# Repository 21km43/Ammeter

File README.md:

# Ammeter
[INA226](https://datasheet.lcsc.com/lcsc/1809192224_Texas-Instruments-INA226AIDGSR_C49851.pdf)を利用した電流計。主にマイコンの消費電流の測定に利用する。  
性能は以下の通り。動作確認済み。
* 入力電圧: 0~36V
* シャント抵抗値: 100mΩ
* 分解能: 25µA
* 電流上限: 819.2mA

ヒューズは入れていないので過電流には注意すること。  
基板CADは[KiCAD](kicad.org)。また、ガーバーファイルはproduction以下に配置した。JLCPCBにアップロードすればすぐに発注可能。

## LICENSE
[MIT LICENSE](/LICENSE)

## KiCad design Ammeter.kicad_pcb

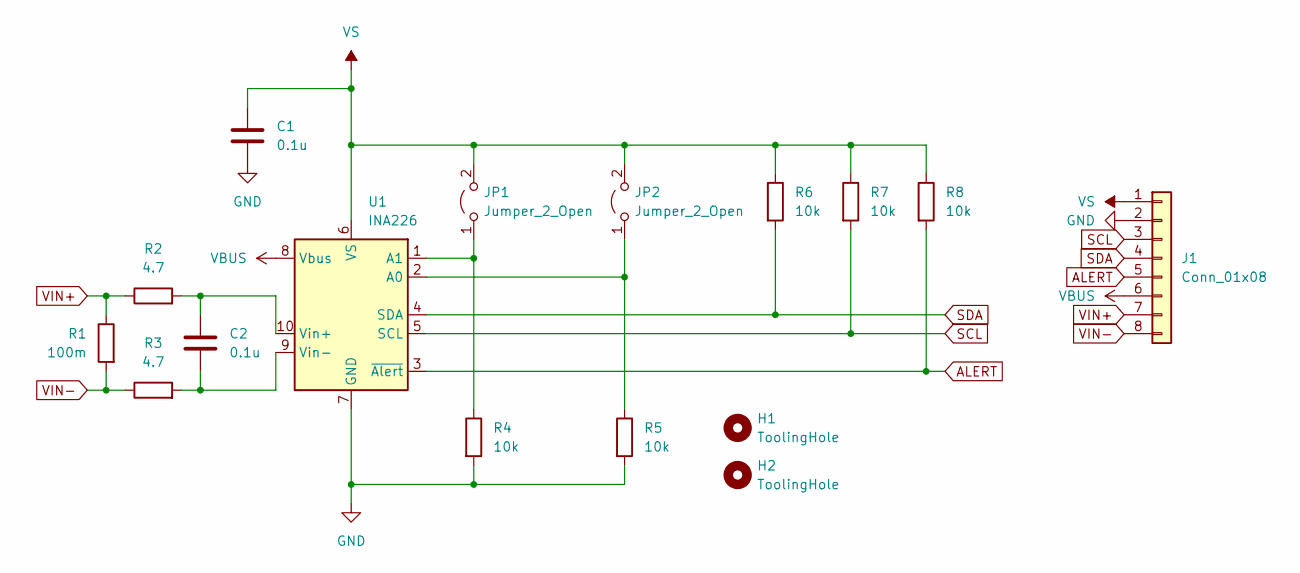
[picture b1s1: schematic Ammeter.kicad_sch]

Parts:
C1, C2: 0.1u; C_0402_1005Metric; LCSC C1525
H1, H2: ToolingHole; Tooling_Hole
J1: Conn_01x08; PinHeader_1x08_P2.54mm_Vertical
JP1, JP2: Jumper_2_Open; SolderJumper-2_P1.3mm_Open_RoundedPad1.0x1.5mm
R1: 100m; R_2512_6332Metric; LCSC C326592
R2, R3: 4.7; R_0603_1608Metric; LCSC C23164
R4, R5, R6, R7, R8: 10k; R_0402_1005Metric; LCSC C25744
U1: INA226; VSSOP-10_3x3mm_P0.5mm; LCSC C49851

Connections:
ALERT: J1.5, R8.2, U1.3 (~Alert)
GND: C1.2, J1.2, R4.2, R5.2, U1.7 (GND)
unnamed: JP1.1 (A), R4.1, U1.1 (A1)
unnamed: JP2.1 (A), R5.1, U1.2 (A0)
unnamed: C2.1, R2.2, U1.10 (Vin+)
unnamed: C2.2, R3.2, U1.9 (Vin-)
SCL: J1.3, R7.2, U1.5 (SCL)
SDA: J1.4, R6.2, U1.4 (SDA)
VBUS: J1.6, U1.8 (Vbus)
VIN+: J1.7, R1.1, R2.1
VIN-: J1.8, R1.2, R3.1
VS: C1.1, J1.1, JP1.2 (B), JP2.2 (B), R6.1, R7.1, R8.1, U1.6 (VS)

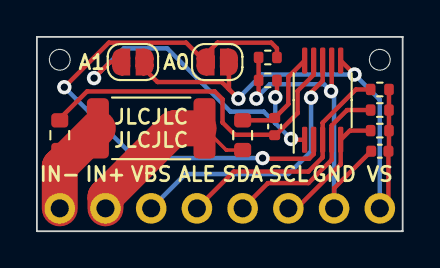
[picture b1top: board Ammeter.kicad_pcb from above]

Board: 2 copper layers, 20.3 x 10.8 mm, 16 parts (1 on the bottom side), 12 nets.

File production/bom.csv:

Designator,Footprint,Quantity,Value,LCSC Part #
"C1, C2",0402,2,0.1u,C1525
R1,2512,1,100m,C326592
"R2, R3",0603,2,4.7,C23164
"R4, R5, R6, R7, R8",0402,5,10k,C25744
U1,VSSOP-10_3x3mm_P0.5mm,1,INA226,C49851
